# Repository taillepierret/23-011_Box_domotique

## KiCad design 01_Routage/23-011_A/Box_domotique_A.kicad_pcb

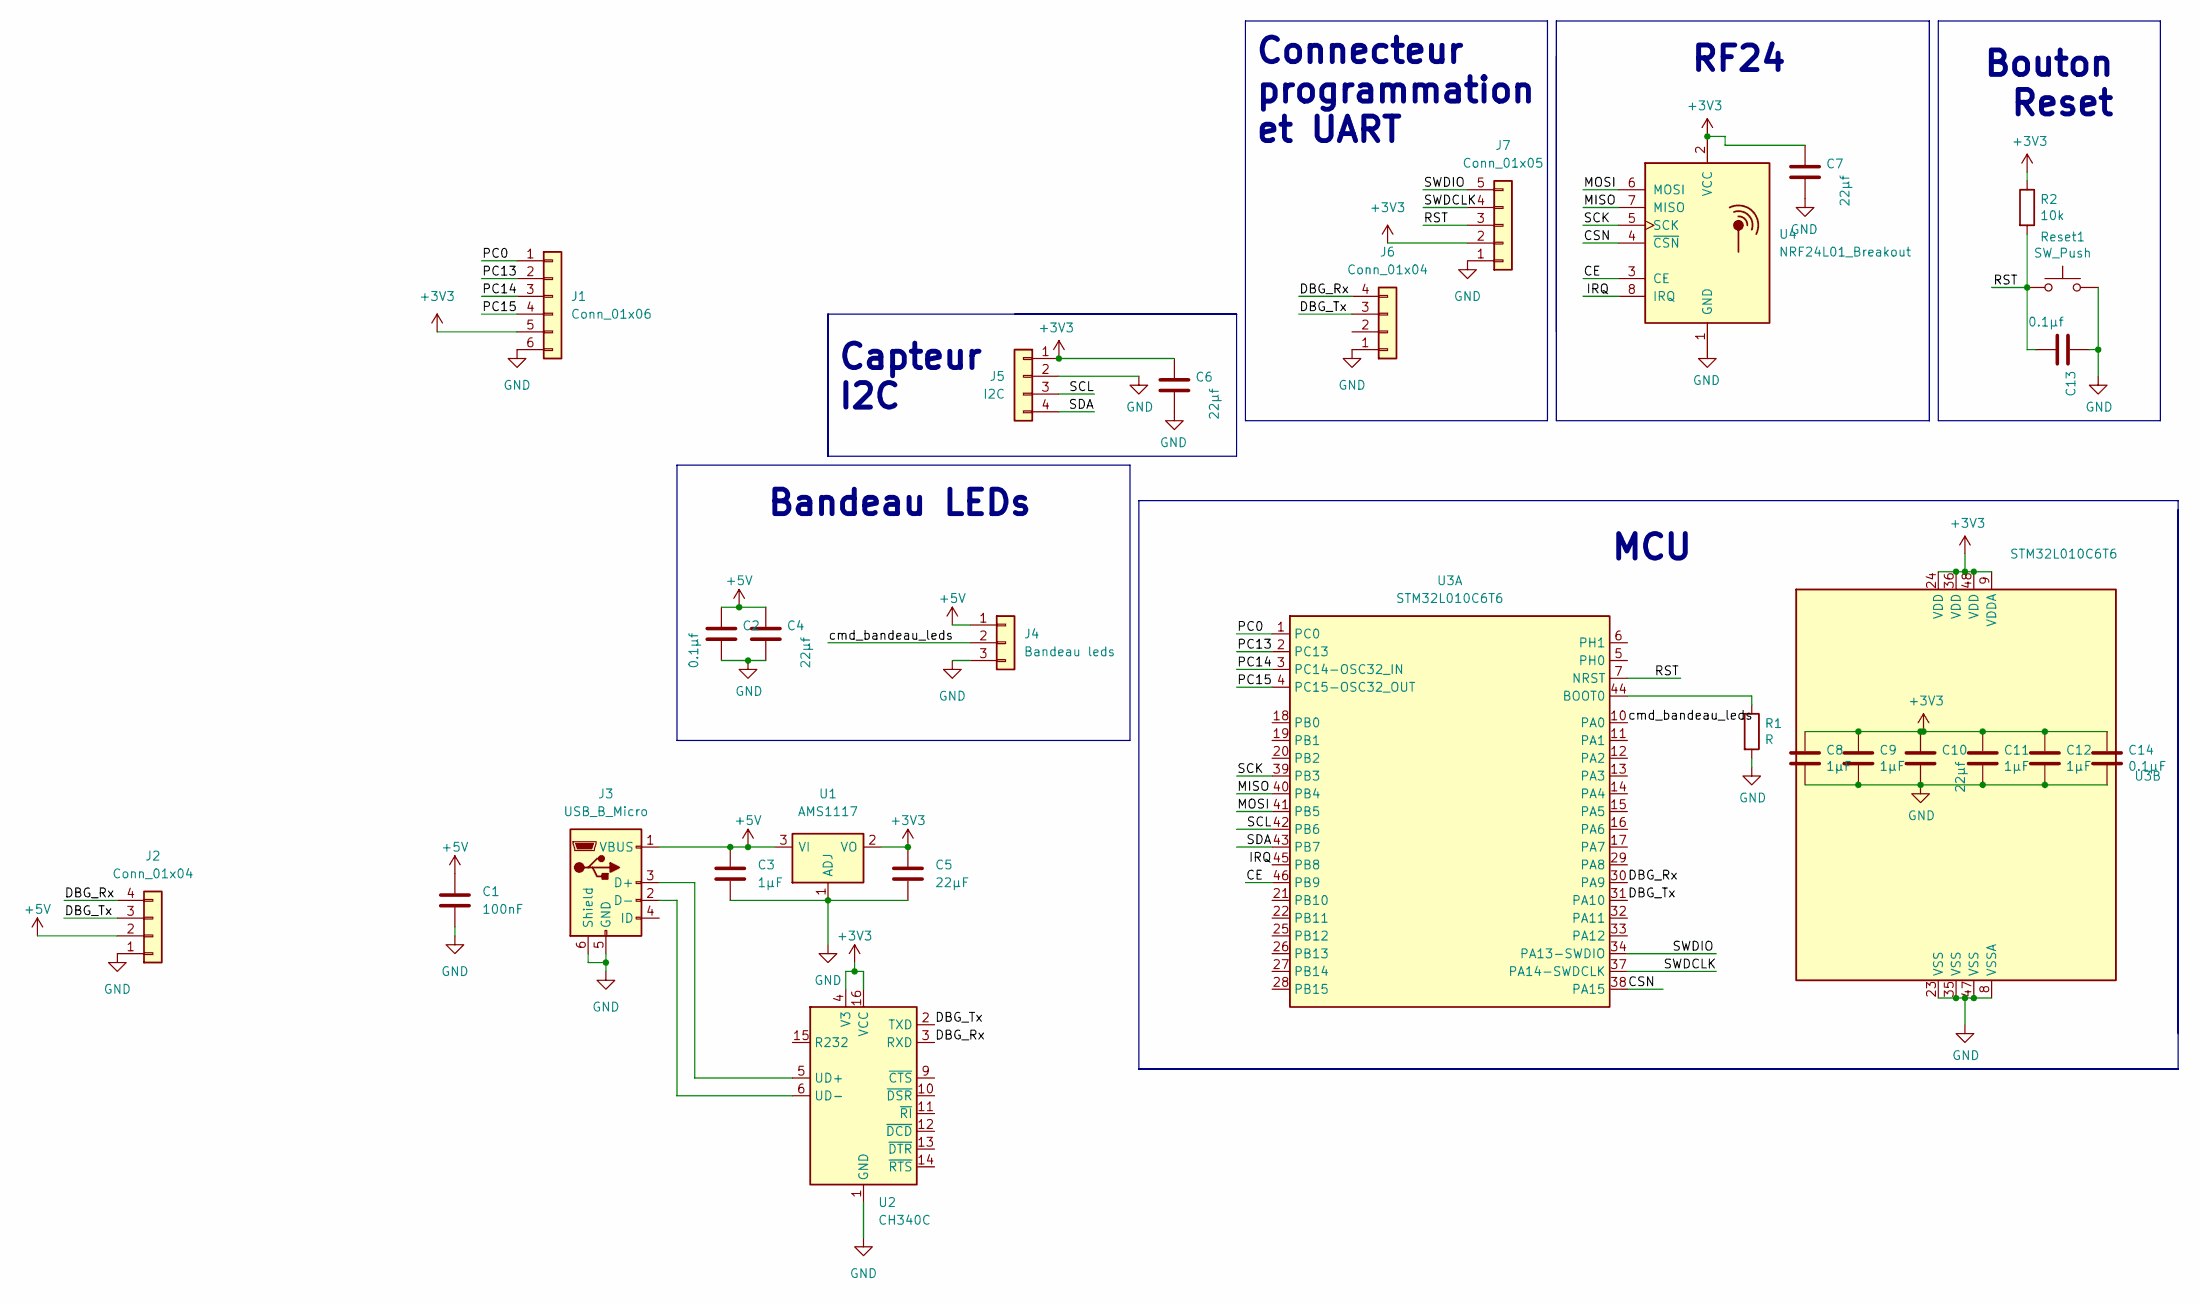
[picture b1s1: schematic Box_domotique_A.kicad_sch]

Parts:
C1: 100nF; C_0603_1608Metric
C2, C13: 0.1µf; C_0603_1608Metric
C3: 1µF; C_0603_1608Metric
C4: 22µf; C_0603_1608Metric
C5: 22µF; C_0603_1608Metric
C6, C7, C10: 22µf; C_0805_2012Metric
C8, C9, C11, C12: 1µF; C_0805_2012Metric
C14: 0.1µF; C_0805_2012Metric
J1: Conn_01x06; PinHeader_1x06_P2.54mm_Vertical
J2: Conn_01x04; PinHeader_1x04_P2.54mm_Vertical
J3: USB_B_Micro; USB_Micro-B_Wuerth_629105150521
J4: Bandeau leds; PinHeader_1x03_P2.54mm_Vertical
J5: I2C; PinHeader_1x04_P2.54mm_Vertical
J6: Conn_01x04; JST_EH_B4B-EH-A_1x04_P2.50mm_Vertical
J7: Conn_01x05; JST_EH_B5B-EH-A_1x05_P2.50mm_Vertical
R1: R; R_0603_1608Metric
R2: 10k; R_0603_1608Metric
Reset1: SW_Push; SW_SPST_CK_RS282G05A3
U1: AMS1117; SOT-223-3_TabPin2
U2: CH340C; SOIC-16_3.9x9.9mm_P1.27mm
U3: STM32L010C6T6; QFP50P900X900X160-48N
U4: NRF24L01_Breakout; nRF24L01_Breakout

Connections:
+3V3: C5.1, C6.1, C7.1, C8.1, C9.1, C10.1, C11.1, C12.1, C14.1, J1.5, J5.1, J7.2, R2.1, U1.2 (VO), U2.4 (V3), U2.16 (VCC), U3.9 (VDDA), U3.24 (VDD), U3.36 (VDD), U3.48 (VDD), U4.2 (VCC)
+5V: C1.1, C2.1, C3.1, C4.1, J2.2, J3.1 (VBUS), J4.1, U1.3 (VI)
/CE: U3.46 (PB9), U4.3 (CE)
/CSN: U3.38 (PA15), U4.4 (~CSN)
/DBG_Rx: J2.4, J6.4, U2.3 (RXD), U3.30 (PA9)
/DBG_Tx: J2.3, J6.3, U2.2 (TXD), U3.31 (PA10)
/IRQ: U3.45 (PB8), U4.8 (IRQ)
/MISO: U3.40 (PB4), U4.7 (MISO)
/MOSI: U3.41 (PB5), U4.6 (MOSI)
/PC0: J1.1, U3.1 (PC0)
/PC13: J1.2, U3.2 (PC13)
/PC14: J1.3, U3.3 (PC14-OSC32_IN)
/PC15: J1.4, U3.4 (PC15-OSC32_OUT)
/RST: C13.2, J7.3, R2.2, Reset1.1, U3.7 (NRST)
/SCK: U3.39 (PB3), U4.5 (SCK)
/SCL: J5.3, U3.42 (PB6)
/SDA: J5.4, U3.43 (PB7)
/SWDCLK: J7.4, U3.37 (PA14-SWDCLK)
/SWDIO: J7.5, U3.34 (PA13-SWDIO)
/cmd_bandeau_leds: J4.2, U3.10 (PA0)
GND: C1.2, C2.2, C3.2, C4.2, C5.2, C6.2, C7.2, C8.2, C9.2, C10.2, C11.2, C12.2, C13.1, C14.2, J1.6, J2.1, J3.5 (GND), J3.6 (Shield), J4.3, J5.2, J6.1, J7.1, R1.2, Reset1.2, U1.1 (ADJ), U2.1 (GND), U3.8 (VSSA), U3.23 (VSS), U3.35 (VSS), U3.47 (VSS), U4.1 (GND)
unnamed: J3.2 (D-), U2.6 (UD-)
unnamed: J3.3 (D+), U2.5 (UD+)
unnamed: R1.1, U3.44 (BOOT0)

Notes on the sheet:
Bandeau LEDs
MCU
Connecteur programmation et UART
RF24
Bouton Reset
Capteur I2C

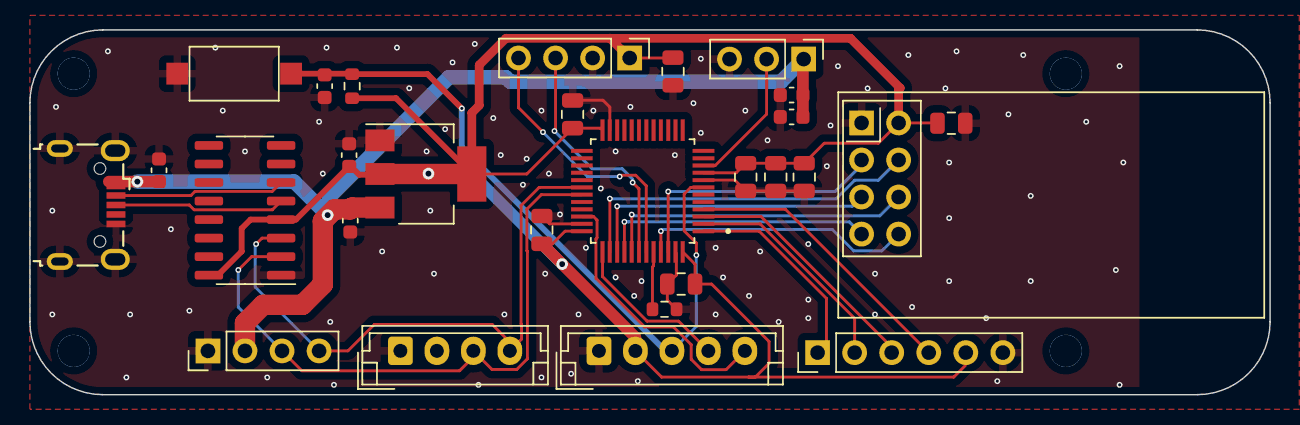
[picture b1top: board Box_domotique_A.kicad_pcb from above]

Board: 2 copper layers, 85.0 x 25.0 mm, 28 parts (0 on the bottom side), 24 nets.

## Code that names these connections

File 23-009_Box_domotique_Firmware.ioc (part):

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Mcu.Name=STM32L010C6Tx
Mcu.Package=LQFP48
Mcu.UserName=STM32L010C6Tx
PA10.Mode=Asynchronous
PA10.Signal=USART2_RX
PA15.GPIOParameters=GPIO_Label
PA15.GPIO_Label=CSN
PA15.Signal=GPIO_Output
PA9.Mode=Asynchronous
PA9.Signal=USART2_TX
PB3.Mode=Full_Duplex_Master
PB3.Signal=SPI1_SCK
PB4.Mode=Full_Duplex_Master
PB4.Signal=SPI1_MISO
PB5.Mode=Full_Duplex_Master
PB5.Signal=SPI1_MOSI
PB8.GPIOParameters=GPIO_Label
PB8.GPIO_Label=IRQ
PB8.Signal=GPIO_Output
PB9.GPIOParameters=GPIO_Label
PB9.GPIO_Label=CE
PB9.Signal=GPIO_Output
RCC.HSE_VALUE=8000000
RCC.SYSCLKFreq_VALUE=2097000
board=custom

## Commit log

2023-10-03 Rx et Tx fonctionnel avec le code de controllerstech
2023-10-04 ajout fonctionnels
2023-10-04 ajouts fonctionnels
2023-10-04 ajouts fonctionnels pour le RX
2023-10-07 Fonctionnel pou rle RX mais pas le Tx
2023-10-07 Ajout du calcul du crc8
2023-10-15 Fonctionnel: le pb était que dans le send le cs était reset au mauvais moment
2023-10-15 cration du ping, de l'init et de quoi tester tout ca
2023-10-15 ajout du code de test: ne marche pas
2023-10-15 bug fix
2023-10-15 Tx fonctionnel
2023-10-15 Bug fix on set Txmode
2023-10-15 Bug fix on receive packet and print packet; print packer not ended
2023-10-15 ajout d'une focntion d'affichage d'un uint32_t, bug fix mineure, ajout de la taille de payload en constante, mùodification de la fonction static d'envoi et meilleur affichage des paquets recus
2023-10-15 test d'emission juste après reception, fonction ack faite masi son payload ne semble pas bon
2023-10-16 ajout de la state machine pour l'envoie de paquet, la reception n'a pas été gérée, faire une fonction qui attend un message de retour après envoie (comme ce que j'ai fait en uart avec le module quect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
2023-10-16 debut de l'ajout de la gestion des paquets Rx
2023-10-22 enregistrement du paquet recu dans la stack de buffers de reception, seulement si le paquet nous est bien adressé et que le crc est bon (non testé)
2023-10-27 creation du process Rx et un autre Tx a executer en //, fonction de process qui appelle les deux precedents
2023-10-27 mini bug fix
2023-10-27 ajout du test de ce que j'ai fait
2023-10-28 Ajout des fonctions de debug avec un niveau de debug, modification de la procedure de test,bug fix: on attends plus le timeout ack pouir un pacquet ack (le seul paquet qui n'attend pas de ack ...), g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
2023-10-28 ajotu de commentaires
2023-10-28 ajout de retry si pas d'ACK recu, Timeout attente ACK passé à 5secondes,
2023-10-29 ajout du stockage en ram des erreur à faire plus tard dans eeprom
2023-10-29 ajout du process pour gerer les commandes de dbg, ajout de la rtc en mode calendrier
2023-11-01 ajout de la gestion de commande de debug en UART DMA, bugfix sur la ârtie print debug, ajout de la dma dans la HAL, optimisation mémoire
2023-11-04 ajout de la rtc pour le debug (ne marche pas) et des optimisations
2024-07-17 ajout des fichiers de routage (nouvel init du projet)
2024-07-17 added project
2024-07-17 done
2024-07-17 reste plus qu'à faire le cmake.tkt
2024-07-28 utilisation de cubeide + finalisation du debug en ecriture
2024-07-31 commandes de log
2024-07-31 continuation
2024-08-01 update gitignore
2024-08-01 ajotu de la reception uart mais blqoue sur le crc pas valide
2024-08-02 lib log ok
2024-08-02 ajout du timeout lors du traitement des logs + nettoyage
2024-08-04 bug fix, passage en mode rx et tx quand il faut
2024-08-04 improvements
2024-08-05 légé bug fix
